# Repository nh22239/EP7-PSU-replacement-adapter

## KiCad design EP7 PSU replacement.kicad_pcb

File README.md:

# EP7 adapter

A friend of mine found a Studiomaster Trilogy 166 mixing desk at a tip sale, unfortunately it came without it's original power supply. My friend sent me the electrical diagrams for the power supply and asked me if I could build one, but that would be too much of a job, so I offered to make a MacGyver version.

## Requirements

The original power supply, called EP7, takes mains power and spits out +/-17V (900mA) and 48V (100mA) through a 5-pin 240-degree dip jack. This is somewhat awkward, but I have a solution....

## Solution

I will take two +17V DC power supplies, and one +48V power supply, and build a circuit that combines these into the dip jack that my friend's mixing desk wants.

I have included a few additional features here, namely noise reduction on each power line, an on/off switch to help avoid lobsided power, a delay on the 48V line to stop any pops from this supply, and some resistors to discharge everything when powered off.

Some of these additions may be useless, and there may be some sensible features that I have failed to put in, but at least this shouldn't break any of my friend's gear.

## UPDATE 18/02/25

Big oops... capacitor C6 is the wrong way round here, it exploded on my finger when I plugged it in... In addition, the DC jacks I bought are wired differently to the standard ones in KiCad... so here I am with a stinging finger, cutting tracks and throwing new wires. Updated circuit diagram to come.

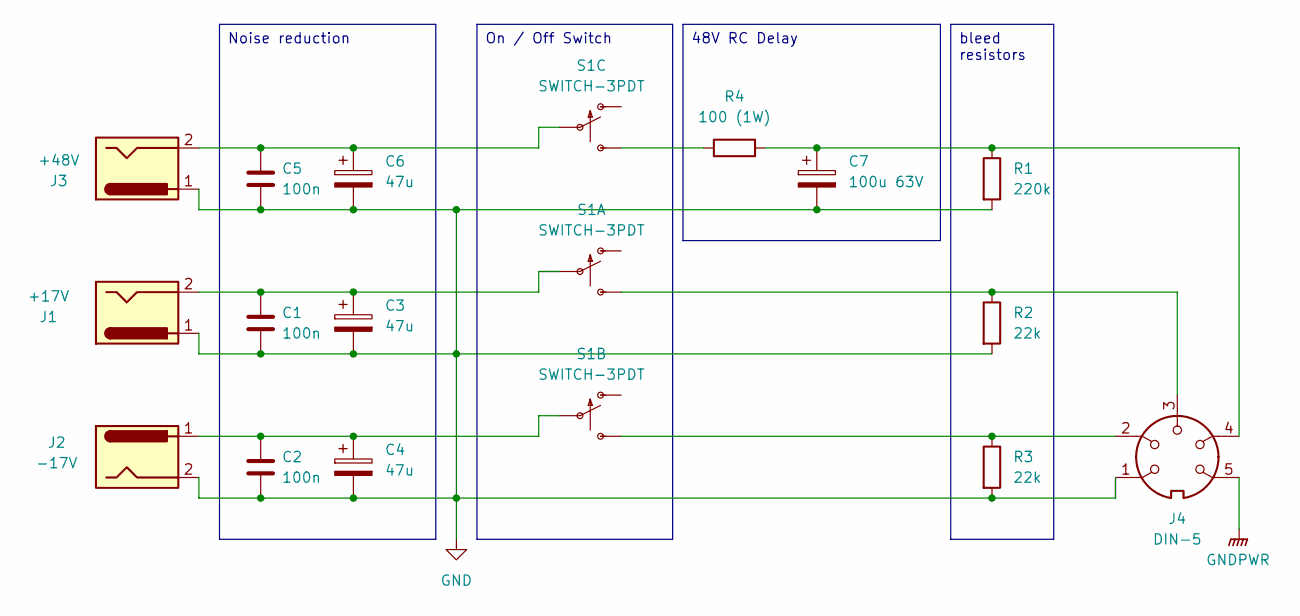
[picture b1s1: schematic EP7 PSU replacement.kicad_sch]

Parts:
C1, C2, C5: 100n; C_Axial_L3.8mm_D2.6mm_P7.50mm_Horizontal
C3, C4, C6: 47u; CP_Radial_D4.0mm_P2.00mm
C7: 100u 63V; CP_Radial_D4.0mm_P2.00mm
J1: +17V; BarrelJack_Horizontal
J2: -17V; BarrelJack_Horizontal
J3: +48V; BarrelJack_Horizontal
J4: DIN-5; SolderWire-1sqmm_1x05_P5.4mm_D1.4mm_OD2.7mm_Relief
R1: 220k; R_Axial_DIN0207_L6.3mm_D2.5mm_P7.62mm_Horizontal
R2, R3: 22k; R_Axial_DIN0207_L6.3mm_D2.5mm_P7.62mm_Horizontal
R4: 100 (1W); R_Axial_DIN0207_L6.3mm_D2.5mm_P7.62mm_Horizontal
S1: SWITCH-3PDT; STOMP-SWITCH-3PDT

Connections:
GND: C1.2, C2.2, C3.2, C4.2, C5.2, C6.2, C7.2, J1.1, J2.2, J3.1, J4.1, R1.2, R2.2, R3.2
GNDPWR: J4.5
unnamed: C7.1, J4.4, R1.1, R4.2
unnamed: C1.1, C3.1, J1.2, S1.P$2
unnamed: J4.3, R2.1, S1.P$3 (S)
unnamed: C2.1, C4.1, J2.1, S1.P$5
unnamed: J4.2, R3.1, S1.P$6 (S)
unnamed: C5.1, C6.1, J3.2, S1.P$8
unnamed: R4.1, S1.P$9 (S)

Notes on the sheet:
Noise reduction
48V RC Delay
bleed resistors
On / Off Switch

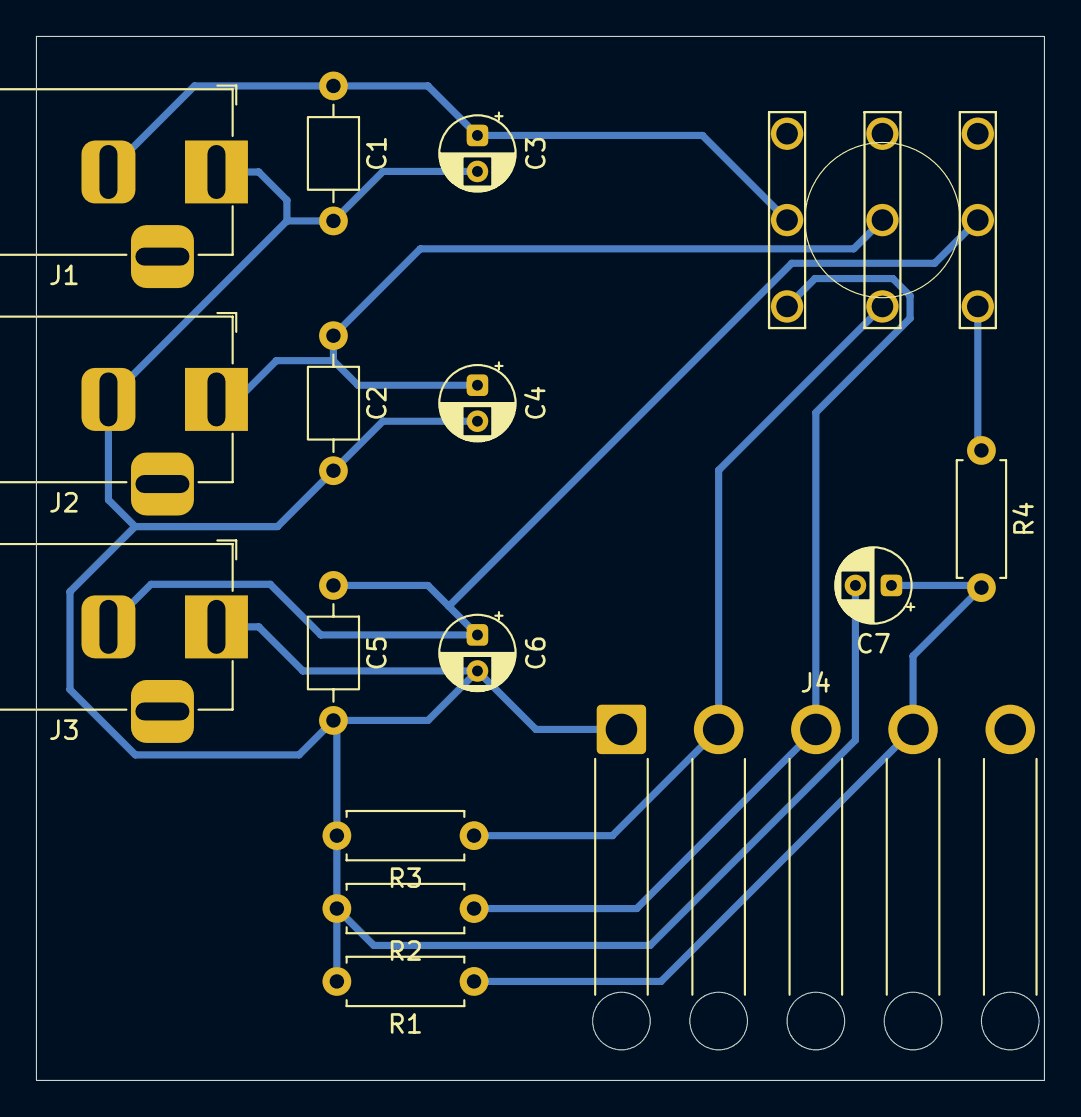
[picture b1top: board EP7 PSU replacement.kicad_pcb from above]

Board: 2 copper layers, 56.0 x 58.0 mm, 16 parts (0 on the bottom side), 8 nets.

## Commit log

2026-02-18 Document update on capacitor and wiring issues
    Added update about capacitor orientation and DC jack wiring issues.
